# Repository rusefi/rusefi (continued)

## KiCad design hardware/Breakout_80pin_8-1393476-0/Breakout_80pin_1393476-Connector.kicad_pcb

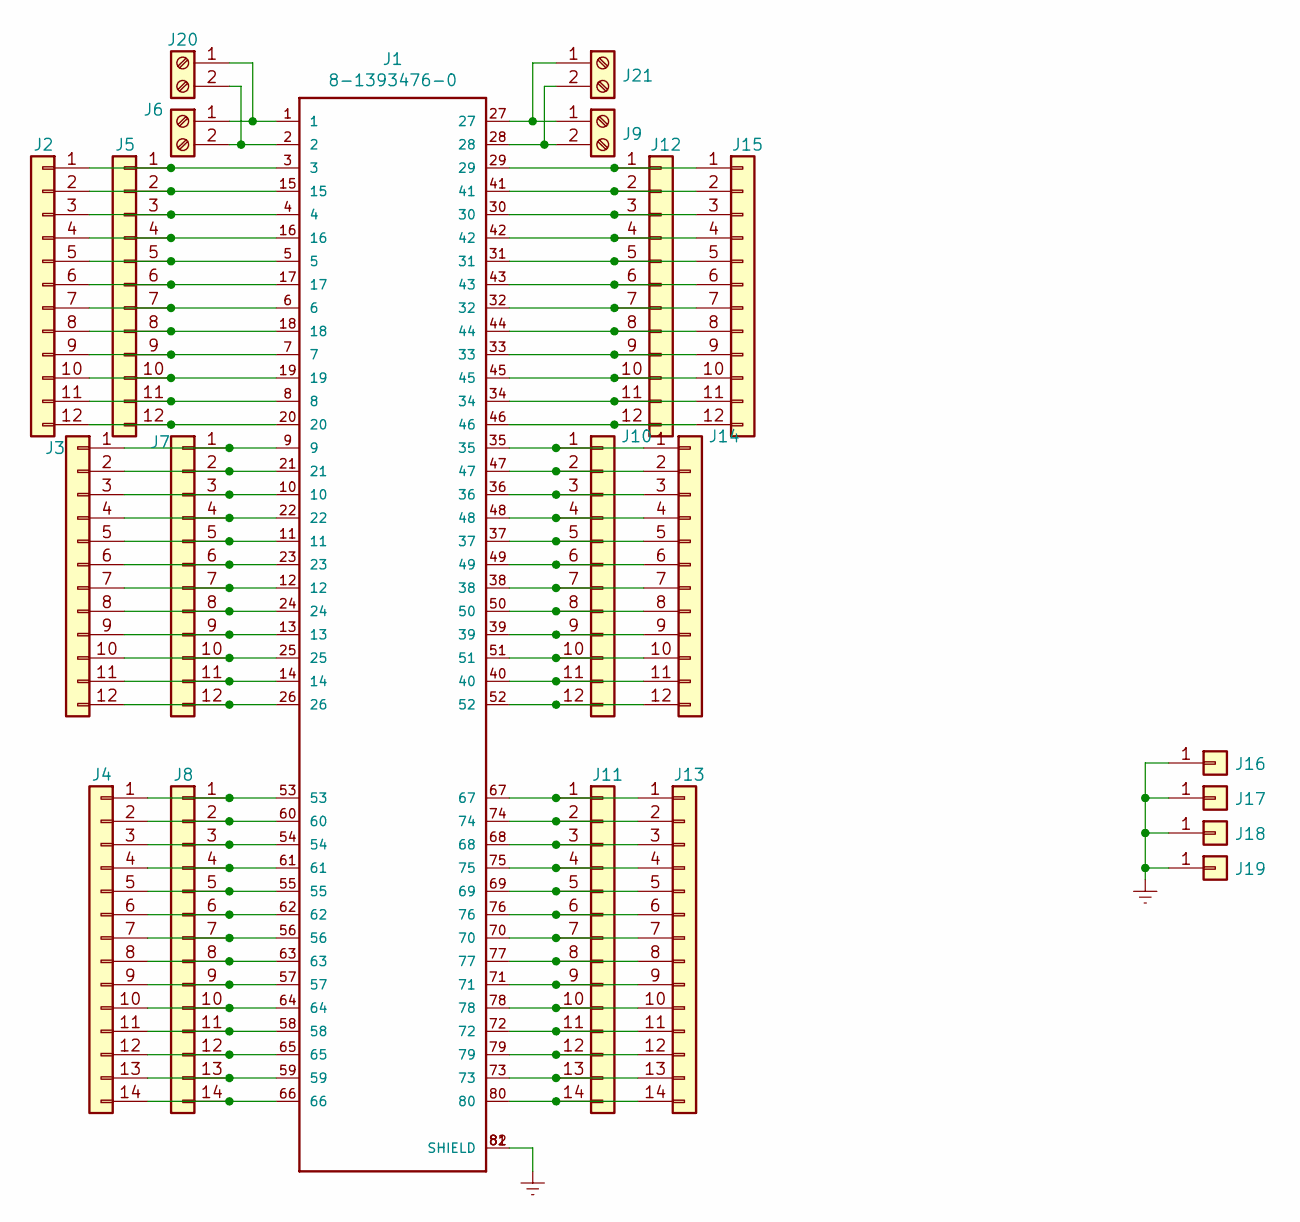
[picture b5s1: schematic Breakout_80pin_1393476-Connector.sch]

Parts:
J1: 8-1393476-0
J2, J3, J5, J7, J10, J12, J14, J15: Conn_01x12; Pin_Header_Straight_1x12_Pitch2.54mm
J4, J8, J11, J13: Conn_01x14; Pin_Header_Straight_1x14_Pitch2.54mm
J6, J9, J20, J21: Screw_Terminal_01x02; WireConnection_2.50mmDrill
J16, J17, J18, J19: Conn_01x01; Pin_Header_Straight_1x01_Pitch2.54mm

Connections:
Earth: J1.81 (SHIELD), J1.82 (SHIELD), J16.1, J17.1, J18.1, J19.1
unnamed: J1.1, J6.1, J20.1
unnamed: J1.2, J6.2, J20.2
unnamed: J1.3, J2.1, J5.1
unnamed: J1.4, J2.3, J5.3
unnamed: J1.5, J2.5, J5.5
unnamed: J1.6, J2.7, J5.7
unnamed: J1.7, J2.9, J5.9
unnamed: J1.8, J2.11, J5.11
unnamed: J1.9, J3.1, J7.1
unnamed: J1.10, J3.3, J7.3
unnamed: J1.11, J3.5, J7.5
unnamed: J1.12, J3.7, J7.7
unnamed: J1.13, J3.9, J7.9
unnamed: J1.14, J3.11, J7.11
unnamed: J1.15, J2.2, J5.2
unnamed: J1.16, J2.4, J5.4
unnamed: J1.17, J2.6, J5.6
unnamed: J1.18, J2.8, J5.8
unnamed: J1.19, J2.10, J5.10
unnamed: J1.20, J2.12, J5.12
unnamed: J1.21, J3.2, J7.2
unnamed: J1.22, J3.4, J7.4
unnamed: J1.23, J3.6, J7.6
unnamed: J1.24, J3.8, J7.8
unnamed: J1.25, J3.10, J7.10
unnamed: J1.26, J3.12, J7.12
unnamed: J1.27, J9.1, J21.1
unnamed: J1.28, J9.2, J21.2
unnamed: J1.29, J12.1, J15.1
unnamed: J1.30, J12.3, J15.3
unnamed: J1.31, J12.5, J15.5
unnamed: J1.32, J12.7, J15.7
unnamed: J1.33, J12.9, J15.9
unnamed: J1.34, J12.11, J15.11
unnamed: J1.35, J10.1, J14.1
unnamed: J1.36, J10.3, J14.3
unnamed: J1.37, J10.5, J14.5
unnamed: J1.38, J10.7, J14.7
unnamed: J1.39, J10.9, J14.9
unnamed: J1.40, J10.11, J14.11
unnamed: J1.41, J12.2, J15.2
unnamed: J1.42, J12.4, J15.4
unnamed: J1.43, J12.6, J15.6
unnamed: J1.44, J12.8, J15.8
unnamed: J1.45, J12.10, J15.10
unnamed: J1.46, J12.12, J15.12
unnamed: J1.47, J10.2, J14.2
unnamed: J1.48, J10.4, J14.4
unnamed: J1.49, J10.6, J14.6
unnamed: J1.50, J10.8, J14.8
unnamed: J1.51, J10.10, J14.10
unnamed: J1.52, J10.12, J14.12
unnamed: J1.53, J4.1, J8.1
unnamed: J1.54, J4.3, J8.3
unnamed: J1.55, J4.5, J8.5
unnamed: J1.56, J4.7, J8.7
unnamed: J1.57, J4.9, J8.9
unnamed: J1.58, J4.11, J8.11
unnamed: J1.59, J4.13, J8.13
unnamed: J1.60, J4.2, J8.2
unnamed: J1.61, J4.4, J8.4
unnamed: J1.62, J4.6, J8.6
unnamed: J1.63, J4.8, J8.8
unnamed: J1.64, J4.10, J8.10
unnamed: J1.65, J4.12, J8.12
unnamed: J1.66, J4.14, J8.14
unnamed: J1.67, J11.1, J13.1
unnamed: J1.68, J11.3, J13.3
unnamed: J1.69, J11.5, J13.5
unnamed: J1.70, J11.7, J13.7
unnamed: J1.71, J11.9, J13.9
unnamed: J1.72, J11.11, J13.11
unnamed: J1.73, J11.13, J13.13
unnamed: J1.74, J11.2, J13.2
unnamed: J1.75, J11.4, J13.4
unnamed: J1.76, J11.6, J13.6
unnamed: J1.77, J11.8, J13.8
unnamed: J1.78, J11.10, J13.10
unnamed: J1.79, J11.12, J13.12
unnamed: J1.80, J11.14, J13.14

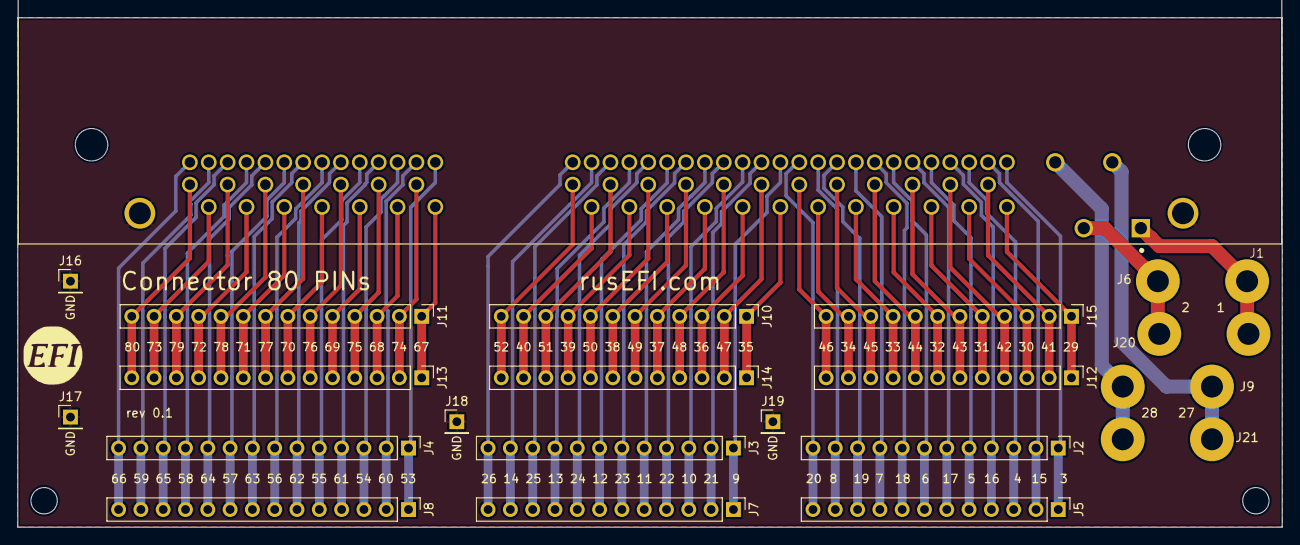
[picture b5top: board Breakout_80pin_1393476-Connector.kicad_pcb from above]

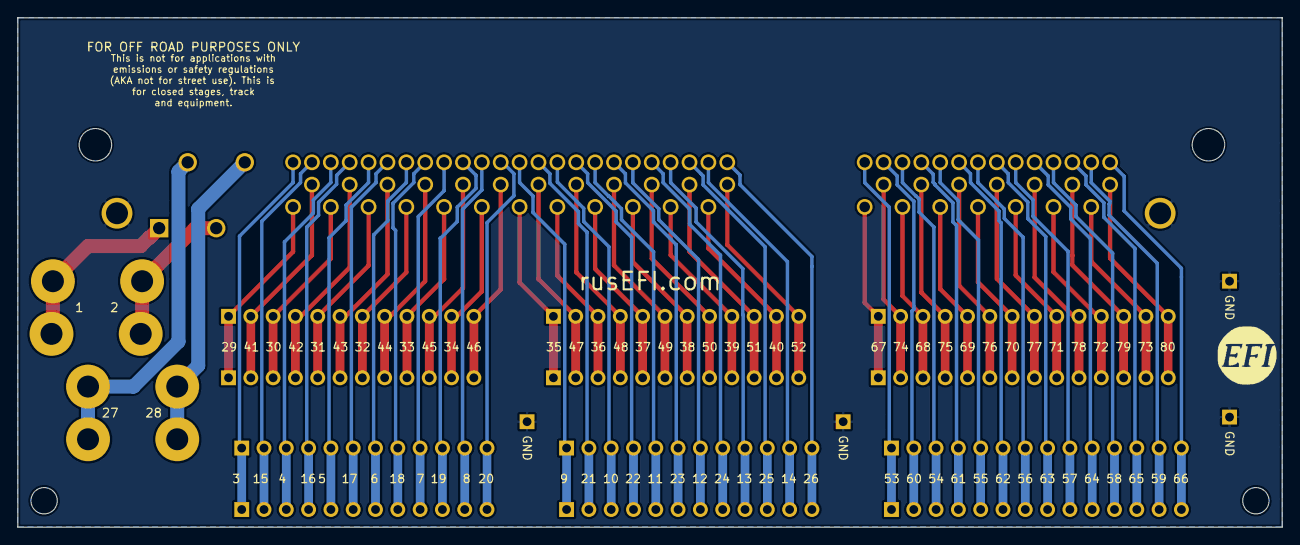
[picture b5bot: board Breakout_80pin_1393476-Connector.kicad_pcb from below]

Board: 2 copper layers, 144.0 x 58.0 mm, 24 parts (2 on the bottom side), 81 nets.

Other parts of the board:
G?: Disclaimer; Off_Road_Disclaimer
G?#2, G?#3: LOGO

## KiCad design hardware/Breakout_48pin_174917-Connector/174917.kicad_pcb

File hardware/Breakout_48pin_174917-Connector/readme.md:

48 pin breakout for Miata NA

As of March 2020 this was NEVER populated. Silkscreen might be not finished.

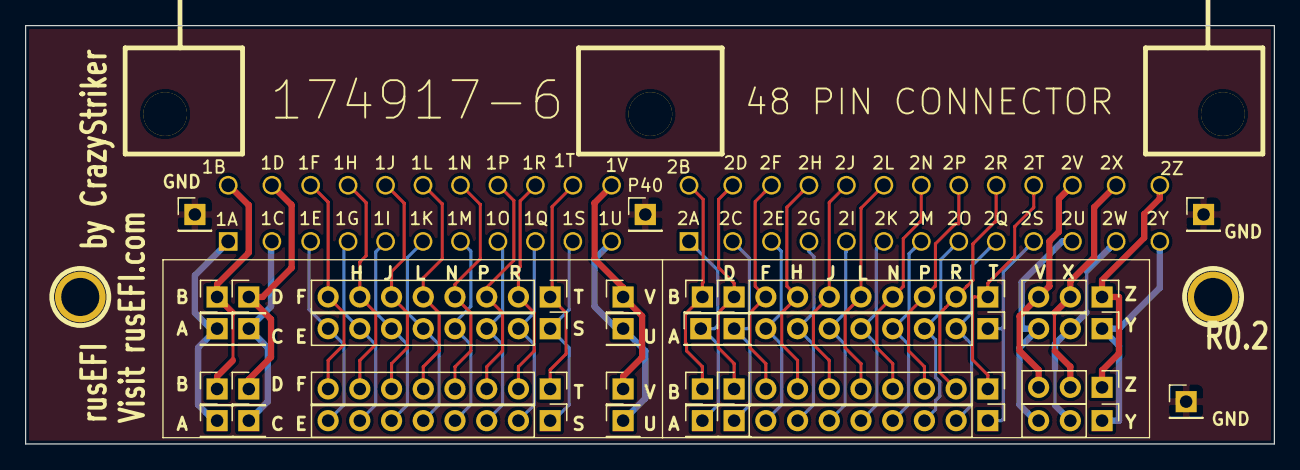
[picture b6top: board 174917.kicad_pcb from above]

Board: 2 copper layers, 100.0 x 33.5 mm, 39 parts (0 on the bottom side), 49 nets.

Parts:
1PIN, 1PIN#2: P***; 1pin
P1, P2, P13, P14: CONN_3; PinHeader_1x03_P2.54mm_Vertical
P3, P4, P5, P6, P7, P8, P9, P10, P11, P12, P15, P16, P17, P18, P19, P20, P21, P22, P23, P24, P38, P39, P40, P41: CONN_1; PinHeader_1x01_P2.54mm_Vertical
P25: 174917
P26, P27, P30, P31, P32, P33, P36, P37: CONN_8; PinHeader_1x08_P2.54mm_Vertical

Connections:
GND: P38.1, P39.1, P40.1, P41.1
unnamed: P1.1, P13.1
unnamed: P1.2, P13.2
unnamed: P1.3, P13.3
unnamed: P10.1, P22.1
unnamed: P11.1, P23.1
unnamed: P12.1, P24.1
unnamed: P2.1, P14.1
unnamed: P2.2, P14.2
unnamed: P2.3, P14.3
unnamed: P3.1, P15.1
unnamed: P4.1, P16.1
unnamed: P5.1, P17.1
unnamed: P6.1, P18.1
unnamed: P7.1, P19.1
unnamed: P8.1, P20.1
unnamed: P9.1, P21.1
unnamed: P26.1, P32.1
unnamed: P26.3, P32.3
unnamed: P26.4, P32.4
unnamed: P26.5, P32.5
unnamed: P26.6, P32.6
unnamed: P26.7, P32.7
unnamed: P26.8, P32.8
unnamed: P27.1, P33.1
unnamed: P27.2, P33.2
unnamed: P27.3, P33.3
unnamed: P27.4, P33.4
unnamed: P27.5, P33.5
unnamed: P27.6, P33.6
unnamed: P27.7, P33.7
unnamed: P27.8, P33.8
unnamed: P30.1, P36.1
unnamed: P30.2, P36.2
unnamed: P30.3, P36.3
unnamed: P30.4, P36.4
unnamed: P30.5, P36.5
unnamed: P30.6, P36.6
unnamed: P30.7, P36.7
unnamed: P30.8, P36.8
unnamed: P31.1, P37.1
unnamed: P31.2, P37.2
unnamed: P31.3, P37.3
unnamed: P31.4, P37.4
unnamed: P31.5, P37.5
unnamed: P31.6, P37.6
unnamed: P31.7, P37.7
unnamed: P31.8, P37.8
unnamed: P26.2, P32.2

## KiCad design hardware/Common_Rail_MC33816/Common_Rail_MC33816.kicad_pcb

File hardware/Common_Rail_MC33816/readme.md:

https://rusefi.com/forum/viewtopic.php?f=4&t=1337

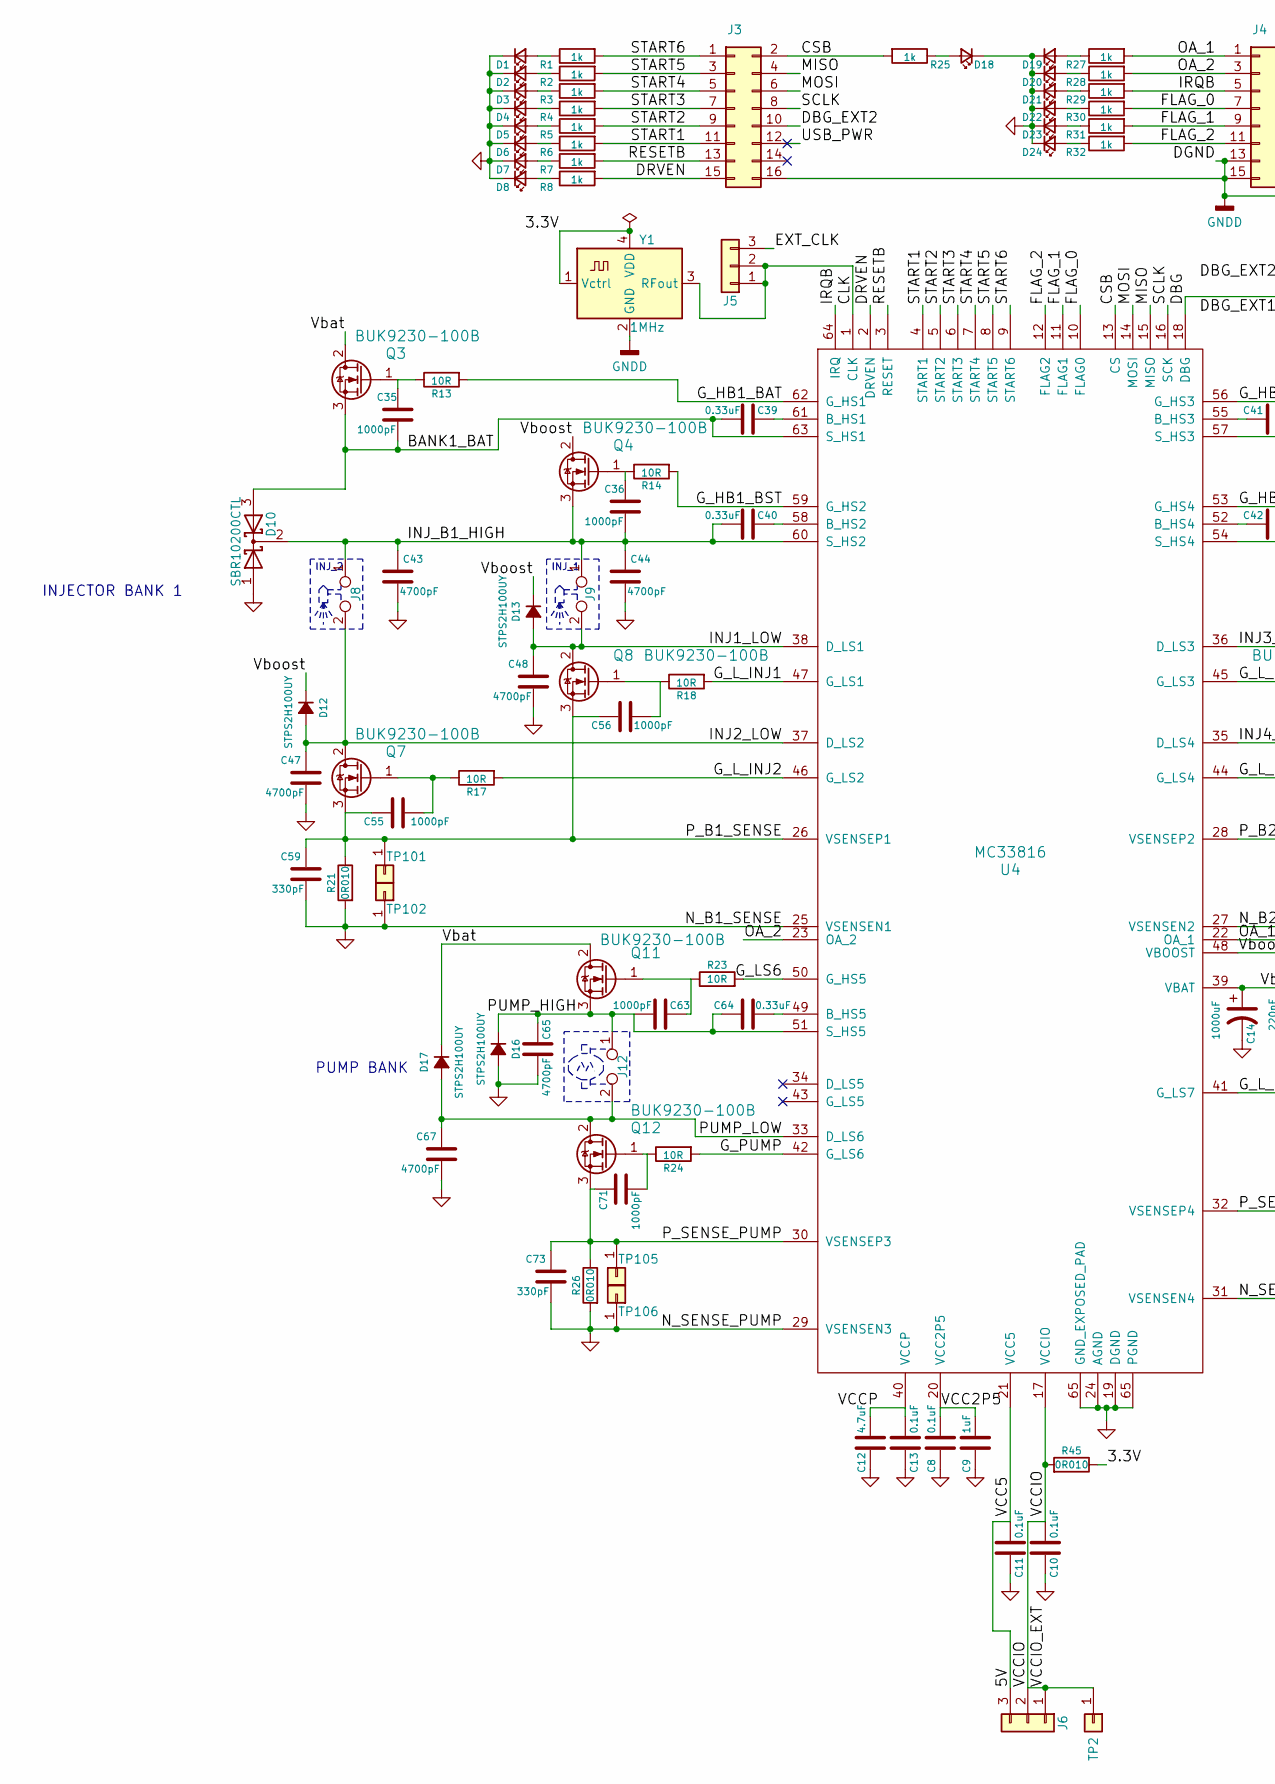
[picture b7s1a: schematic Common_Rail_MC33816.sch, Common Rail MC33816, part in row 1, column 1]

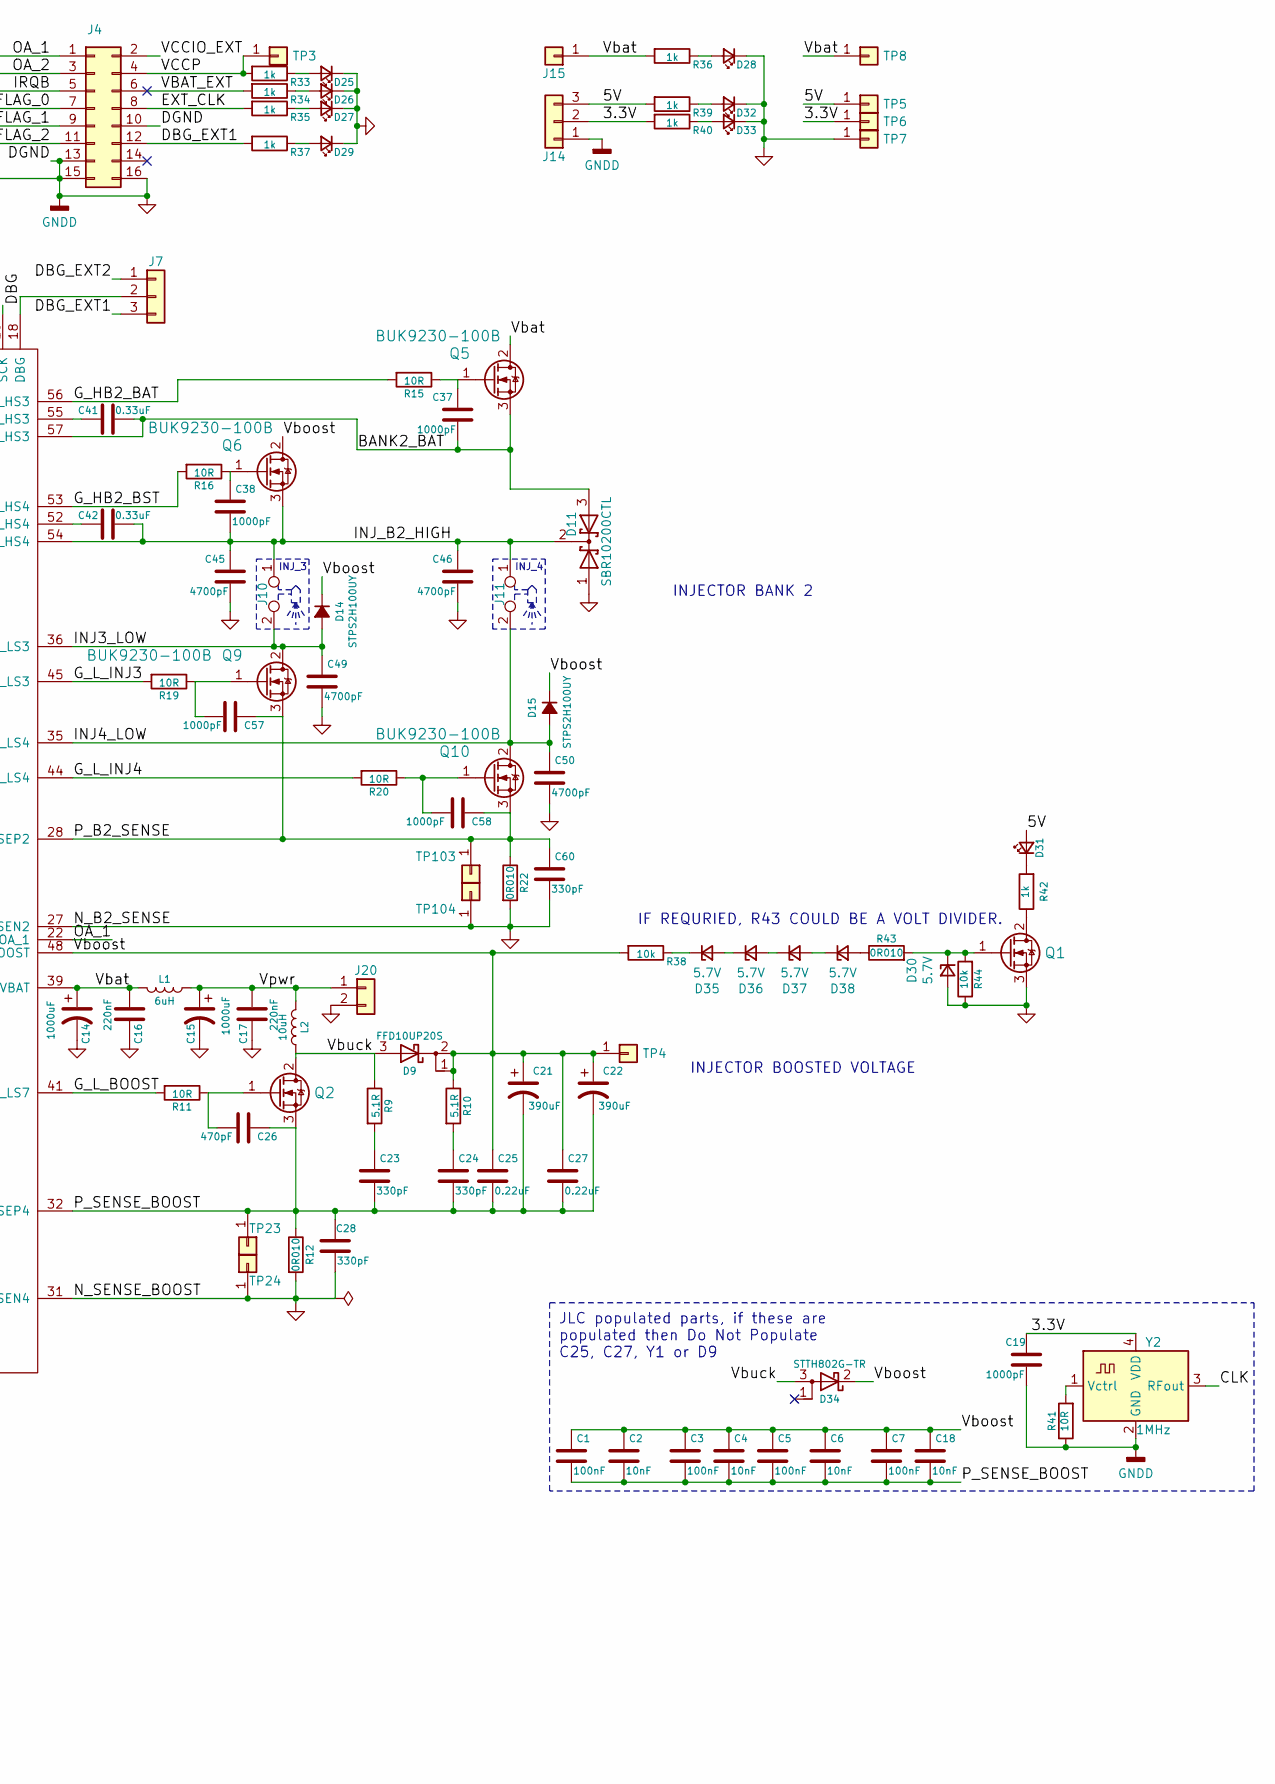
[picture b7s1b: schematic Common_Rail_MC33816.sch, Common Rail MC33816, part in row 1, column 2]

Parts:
C1, C3, C5, C7: 100nF; C_0805; LCSC C28233
C2, C4, C6, C18: 10nF; C_0805; LCSC C18741
C8, C10, C11, C13: 0.1uF; C_0805; LCSC C49678
C9: 1uF; C_0805; LCSC C28323
C12: 4.7uF; C_0805; LCSC C1779
C14, C15: 1000uF; CP_Radial_D22.0mm_P10.00mm_SnapIn
C16, C17: 220nF; C_0805; LCSC C5378
C19, C35, C36, C37, C38, C55, C56, C57, C58, C63, C71: 1000pF; C_0805; LCSC C46653
C21, C22: 390uF; CP_Radial_D16.0mm_P7.50mm
C23, C24, C28, C59, C60, C73: 330pF; C_0805; LCSC C51207
C25, C27: 0.22uF; C_0805
C26: 470pF; C_0805; LCSC C1743
C39, C40, C41, C42, C64: 0.33uF; C_0805; LCSC C1740
C43, C44, C45, C46, C47, C48, C49, C50, C65, C67: 4700pF; C_0805; LCSC C21217
D1, D2, D3, D4, D5, D6, D7, D8, D18, D19, D20, D21, D22, D23, D24, D25, D26, D27, D28, D29, D31, D32, D33: LED_Small; LED_0805_2012Metric; LCSC C2296
D9: FFD10UP20S; TO-252-2
D10, D11: SBR10200CTL; TO-252-2; LCSC C135494
D12, D13, D14, D15, D16, D17: STPS2H100UY; D_SMB; LCSC C157420
D30, D35, D36, D37, D38: 5.7V; D_MicroMELF_Handsoldering; LCSC C8062
D34: STTH802G-TR; TO-263-2; LCSC C181034
J3, J4: CONN_02X08; Pin_Header_Straight_2x08_Pitch2.54mm
J5, J6, J7, J14: CONN_01X03; Pin_Header_Straight_1x03_Pitch2.54mm
J8, J9, J10, J11, J12: INJ_Term; TerminalBlock_bornier-2_P5.08mm
J15: CONN_01X01; Pin_D1.4mm_L8.5mm_W2.8mm_FlatFork
J20: Conn_01x02; TerminalBlock_bornier-2_P5.08mm
L1: 6uH; 744710610-Inductor
L2: 10uH; IHLP6767GZER100M01
Q1, Q2, Q3, Q4, Q5, Q6, Q7, Q8, Q9, Q10, Q11, Q12: BUK9230-100B; TO-252-2; LCSC C67277
R1, R2, R3, R4, R5, R6, R7, R8, R25, R27, R28, R29, R30, R31, R32, R33, R34, R35, R36, R37, R39, R40: 1k; R_0805; LCSC C17513
R9, R10: 5.1R; R_0805; LCSC C247080
R11, R13, R14, R15, R16, R17, R18, R19, R20, R23, R24, R41: 10R; R_0805; LCSC C17415
R12, R21, R22, R26: 0R010; R_1206_HandSoldering; LCSC C76294
R38, R44: 10k; R_0603_1608Metric; LCSC C17513
R42: 1k; R_0805_2012Metric; LCSC C17513
R43, R45: 0R010; R_1206_3216Metric_Pad1.42x1.75mm_HandSolder; LCSC C76294
TP2, TP3, TP4, TP5, TP6, TP7, TP8, TP23, TP24, TP101, TP102, TP103, TP104, TP105, TP106: CONN_01X01; Pin_D0.7mm_L6.5mm_W1.8mm_FlatFork
U4: MC33816; HTQFP-64-1EP_10x10mm_Pitch0.5mm_ThermalPad_for_MC33816
Y1: 1MHz; Crystal_SMD_SeikoEpson_MC306-4pin_8.0x3.2mm
Y2: 1MHz; Oscillator_SMD_Diodes_FN-4Pin_7.0x5.0mm; LCSC C70608

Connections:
/3.3V: C19.1, J14.2, R40.2, R45.1, TP6.1, Y1.1 (Vctrl), Y1.4 (VDD), Y2.4 (VDD)
/5V: C11.1, D31.2 (A), J6.3, J14.3, R39.2, TP5.1, U4.21 (VCC5)
/BANK1_BAT: C35.2, C39.2, D10.3 (A), Q3.3 (S), U4.63 (S_HS1)
/BANK2_BAT: C37.2, C41.2, D11.3 (A), Q5.3 (S), U4.57 (S_HS3)
/CLK: J5.1, J5.2, U4.1 (CLK), Y1.3 (RFout), Y2.3 (RFout)
/CSB: J3.2, R25.2, U4.13 (CS)
/DBG: J7.2, U4.18 (DBG)
/DBG_EXT1: J4.12, J7.3, R37.2
/DBG_EXT2: J3.10, J7.1
/DRVEN: J3.15, R8.2, U4.2 (DRVEN)
/EXT_CLK: J4.8, J5.3, R35.2
/FLAG_0: J4.7, R30.2, U4.10 (FLAG0)
/FLAG_1: J4.9, R31.2, U4.11 (FLAG1)
/FLAG_2: J4.11, R32.2, U4.12 (FLAG2)
/G_HB1_BAT: R13.2, U4.62 (G_HS1)
/G_HB1_BST: R14.2, U4.59 (G_HS2)
/G_HB2_BAT: R15.2, U4.56 (G_HS3)
/G_HB2_BST: R16.2, U4.53 (G_HS4)
/G_LS6: R23.2, U4.50 (G_HS5)
/G_L_BOOST: R11.2, U4.41 (G_LS7)
/G_L_INJ1: R18.2, U4.47 (G_LS1)
/G_L_INJ2: R17.2, U4.46 (G_LS2)
/G_L_INJ3: R19.2, U4.45 (G_LS3)
/G_L_INJ4: R20.2, U4.44 (G_LS4)
/G_PUMP: R24.2, U4.42 (G_LS6)
/INJ1_LOW: C48.1, D13.2 (A), J9.2, Q8.2 (D), U4.38 (D_LS1)
/INJ2_LOW: C47.1, D12.2 (A), J8.2, Q7.2 (D), U4.37 (D_LS2)
/INJ3_LOW: C49.1, D14.2 (A), J10.2, Q9.2 (D), U4.36 (D_LS3)
/INJ4_LOW: C50.1, D15.2 (A), J11.2, Q10.2 (D), U4.35 (D_LS4)
/INJ_B1_HIGH: C36.2, C40.2, C43.1, C44.1, D10.2 (K), J8.1, J9.1, Q4.3 (S), U4.60 (S_HS2)
/INJ_B2_HIGH: C38.2, C42.2, C45.1, C46.1, D11.2 (K), J10.1, J11.1, Q6.3 (S), U4.54 (S_HS4)
/IRQB: J4.5, R29.2, U4.64 (IRQ)
/MISO: J3.4, U4.15 (MISO)
/MOSI: J3.6, U4.14 (MOSI)
/OA_1: J4.1, R27.2, U4.22 (OA_1)
/OA_2: J4.3, R28.2, U4.23 (OA_2)
/PUMP_HIGH: C63.2, C64.1, C65.1, D16.1 (K), J12.1, Q11.3 (S), U4.51 (S_HS5)
/PUMP_LOW: C67.1, D17.2 (A), J12.2, Q12.2 (D), U4.33 (D_LS6)
/P_B1_SENSE: C55.1, C56.1, C59.1, Q7.3 (S), Q8.3 (S), R21.1, TP101.1, U4.26 (VSENSEP1)
/P_B2_SENSE: C57.1, C58.1, C60.1, Q9.3 (S), Q10.3 (S), R22.1, TP103.1, U4.28 (VSENSEP2)
/P_SENSE_BOOST: C1.2, C2.2, C3.2, C4.2, C5.2, C6.2, C7.2, C18.2, C21.2, C22.2, C23.2, C24.2, C25.2, C26.1, C27.2, C28.1, Q2.3 (S), R12.1, TP23.1, U4.32 (VSENSEP4)
/P_SENSE_PUMP: C71.1, C73.1, Q12.3 (S), R26.1, TP105.1, U4.30 (VSENSEP3)
/RESETB: J3.13, R7.2, U4.3 (RESET)
/SCLK: J3.8, U4.16 (SCK)
/START1: J3.11, R6.2, U4.4 (START1)
/START2: J3.9, R5.2, U4.5 (START2)
/START3: J3.7, R4.2, U4.6 (START3)
/START4: J3.5, R3.2, U4.7 (START4)
/START5: J3.3, R2.2, U4.8 (START5)
/START6: J3.1, R1.2, U4.9 (START6)
/VBAT_EXT: J4.6, R34.2
/VCC2P5: C8.1, C9.1, U4.20 (VCC2P5)
/VCCIO: C10.1, J4.2, J6.1, J6.2, R45.2, TP2.1, U4.17 (VCCIO)
/VCCP: C12.1, C13.1, J4.4, R33.2, TP3.1, U4.40 (VCCP)
/Vbat: C14.1, C16.1, D17.1 (K), J15.1, L1.2, Q3.2 (D), Q5.2 (D), Q11.2 (D), R36.2, TP8.1, U4.39 (VBAT)
/Vboost: C1.1, C2.1, C3.1, C4.1, C5.1, C6.1, C7.1, C18.1, C21.1, C22.1, C25.1, C27.1, D9.1 (K), D9.2 (K), D12.1 (K), D13.1 (K), D14.1 (K), D15.1 (K), D34.2 (K), Q4.2 (D), Q6.2 (D), R10.1, R38.2, TP4.1, U4.48 (VBOOST)
/Vbuck: D9.3 (A), D34.3 (A), L2.1, Q2.2 (D), R9.1
/Vpwr: C15.1, C17.1, J20.1, L1.1, L2.2
GND: C8.2, C9.2, C10.2, C11.2, C12.2, C13.2, C14.2, C15.2, C16.2, C17.2, C19.2, C28.2, C43.2, C44.2, C45.2, C46.2, C47.2, C48.2, C49.2, C50.2, C59.2, C60.2, C65.2, C67.2, C73.2, D1.1 (K), D2.1 (K), D3.1 (K), D4.1 (K), D5.1 (K), D6.1 (K), D7.1 (K), D8.1 (K), D10.1 (A), D11.1 (A), D16.2 (A), D18.1 (K), D19.1 (K), D20.1 (K), D21.1 (K), D22.1 (K), D23.1 (K), D24.1 (K), D25.1 (K), D26.1 (K), D27.1 (K), D28.1 (K), D29.1 (K), D30.2 (A), D32.1 (K), D33.1 (K), J3.16, J4.10, J4.13, J4.15, J4.16, J14.1, J20.2, Q1.3 (S), R12.2, R21.2, R22.2, R26.2, R41.1, R44.1, TP7.1, TP24.1, TP102.1, TP104.1, TP106.1, U4.19 (DGND), U4.24 (AGND), U4.25 (VSENSEN1), U4.27 (VSENSEN2), U4.29 (VSENSEN3), U4.31 (VSENSEN4), U4.65 (GND_EXPOSED_PAD), Y1.2 (GND), Y2.2 (GND)
unnamed: C23.1, R9.2
unnamed: C24.1, R10.2
unnamed: C26.2, Q2.1 (G), R11.1
unnamed: C35.1, Q3.1 (G), R13.1
unnamed: C36.1, Q4.1 (G), R14.1
unnamed: C37.1, Q5.1 (G), R15.1
unnamed: C38.1, Q6.1 (G), R16.1
unnamed: C39.1, U4.61 (B_HS1)
unnamed: C40.1, U4.58 (B_HS2)
unnamed: C41.1, U4.55 (B_HS3)
unnamed: C42.1, U4.52 (B_HS4)
unnamed: C55.2, Q7.1 (G), R17.1
unnamed: C56.2, Q8.1 (G), R18.1
unnamed: C57.2, Q9.1 (G), R19.1
unnamed: C58.2, Q10.1 (G), R20.1
unnamed: C63.1, Q11.1 (G), R23.1
unnamed: C64.2, U4.49 (B_HS5)
unnamed: C71.2, Q12.1 (G), R24.1
unnamed: D1.2 (A), R1.1
unnamed: D2.2 (A), R2.1
unnamed: D3.2 (A), R3.1
unnamed: D4.2 (A), R4.1
unnamed: D5.2 (A), R5.1
unnamed: D6.2 (A), R6.1
unnamed: D7.2 (A), R7.1
unnamed: D8.2 (A), R8.1
unnamed: D18.2 (A), R25.1
unnamed: D19.2 (A), R27.1
unnamed: D20.2 (A), R28.1
unnamed: D21.2 (A), R29.1
unnamed: D22.2 (A), R30.1
unnamed: D23.2 (A), R31.1
unnamed: D24.2 (A), R32.1
unnamed: D25.2 (A), R33.1
unnamed: D26.2 (A), R34.1
unnamed: D27.2 (A), R35.1
unnamed: D28.2 (A), R36.1
unnamed: D29.2 (A), R37.1
unnamed: D30.1 (K), Q1.1 (G), R43.2, R44.2
unnamed: D31.1 (K), R42.2
unnamed: D32.2 (A), R39.1
unnamed: D33.2 (A), R40.1
unnamed: D35.1 (K), R38.1
unnamed: D35.2 (A), D36.1 (K)
unnamed: D36.2 (A), D37.1 (K)
unnamed: D37.2 (A), D38.1 (K)
unnamed: D38.2 (A), R43.1
unnamed: Q1.2 (D), R42.1
unnamed: R41.2, Y2.1 (Vctrl)

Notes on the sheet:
PUMP BANK
INJECTOR BOOSTED VOLTAGE
INJECTOR BANK 2
INJECTOR BANK 1
INJ_2
INJ_1
INJ_3
INJ_4
JLC populated parts, if these are populated then Do Not Populate C25, C27, Y1 or D9
IF REQURIED, R43 COULD BE A VOLT DIVIDER.

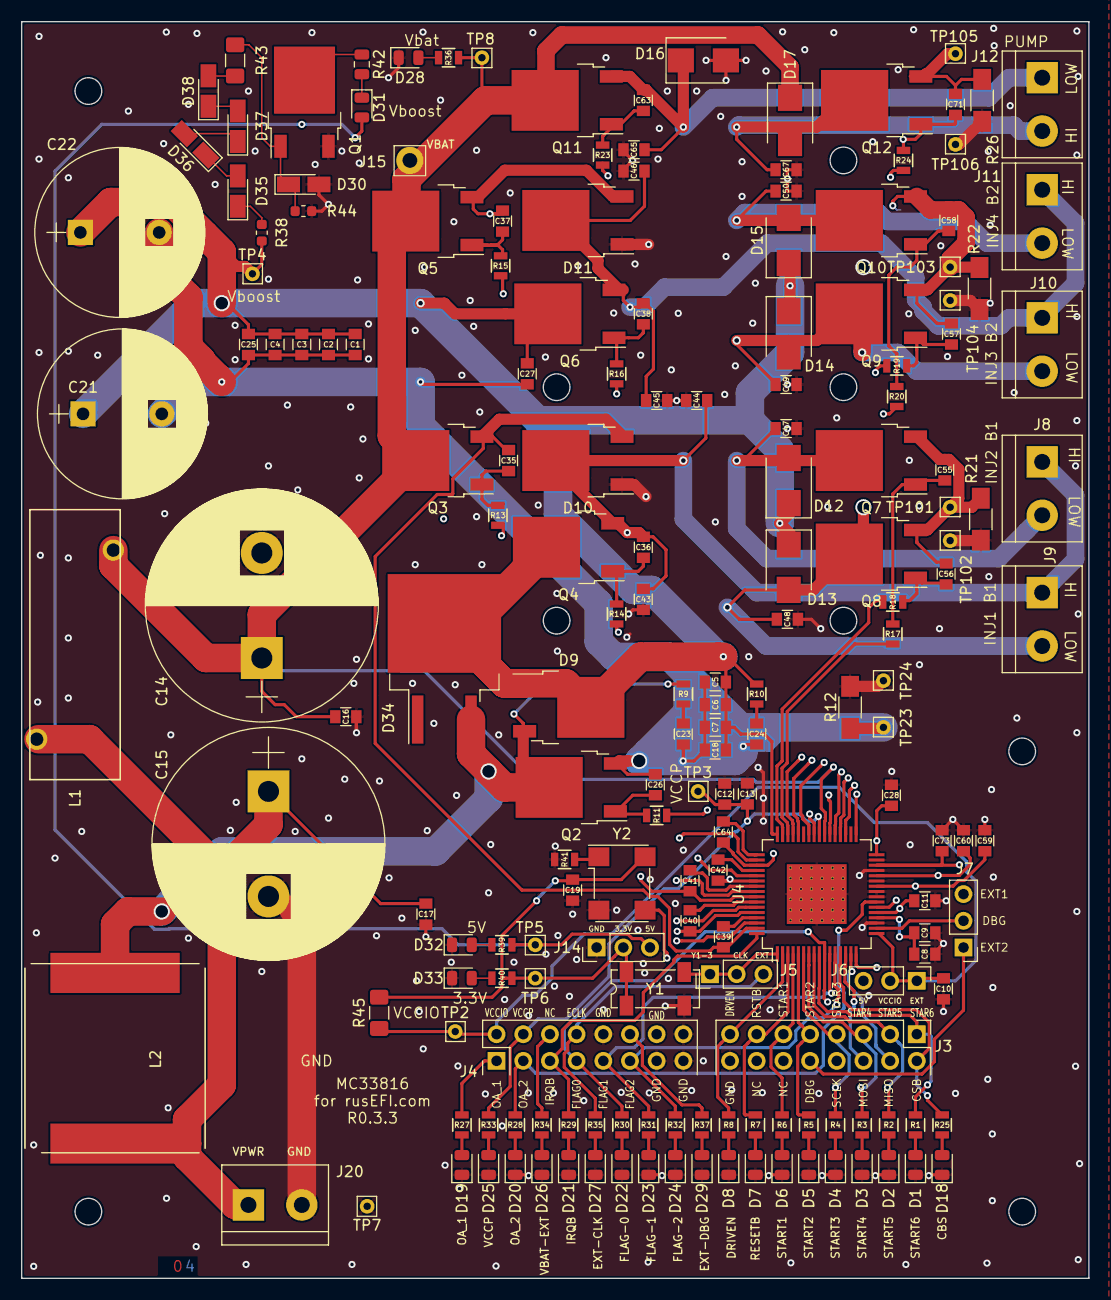
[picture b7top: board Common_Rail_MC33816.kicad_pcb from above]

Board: 4 copper layers, 101.6 x 119.6 mm, 183 parts (0 on the bottom side), 108 nets.

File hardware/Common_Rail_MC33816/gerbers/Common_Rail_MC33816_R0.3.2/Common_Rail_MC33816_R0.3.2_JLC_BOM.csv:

Comment,Designator,Footprint,LCSC, LCSC, MFG,MFG#, VEND1,VEND1#, VEND2,VEND2#
"100nF","C1,C3,C5,C7","rusefi_lib:C_0805","","C28233","","",""
"0.1uF","C10,C11,C13,C8","rusefi_lib:C_0805","","C49678","AVX,08055C104MAT2A","DIGI,478-3351-1-ND","JLCPCB,C49678"
"4.7uF","C12","rusefi_lib:C_0805","","C1779","Taiyo Yuden,TMK212AB7475KG-T","DIGI,587-2990-1-ND","JLCPCB,C1779"
"1000uF","C14,C15","Capacitors_ThroughHole:CP_Radial_D22.0mm_P10.00mm_SnapIn","","","Cornell,SLPX102M100A3P3","DIGI,338-1553-ND",","
"220nF","C17,C16","rusefi_lib:C_0805","","C5378","KEMET,C0805C224M1RACTU","DIGI,399-9205-1-ND",","
"10nF","C2,C4,C6,C18","rusefi_lib:C_0805","","C18741","","",""
"390uF","C21,C22","Capacitors_ThroughHole:CP_Radial_D16.0mm_P7.50mm","","","Nichicon,UHE2A391MHD","DIGI,493-1680-ND",","
"0.22uF","C25,C27","rusefi_lib:C_0805","","","KEMET,C0805C224M1RACTU","DIGI,399-9205-1-ND",","
"470pF","C26","rusefi_lib:C_0805","","C1743","TDK,CGA4C2C0G2A471J060AA","DIGI,445-6953-1-ND","JLCPCB,C1743"
"1000pF","C38,C37,C57,C58,C63,C71,C36,C35,C56,C55,C19","rusefi_lib:C_0805","","C46653","avx,08051C102KAT2A","DIGI,478-1352-1-ND","JLCPCB,C209838"
"0.33uF","C41,C64,C39,C40,C42","rusefi_lib:C_0805","","C1740","Yageo,CC0805KKX7R8BB334","DIGI,311-3385-1-ND","JLCPCB,C1740"
"4700pF","C45,C49,C46,C50,C65,C67,C44,C48,C43,C47","rusefi_lib:C_0805","","C21217","TDK,C2012C0G2A472J125AA","DIGI,445-2324-1-ND","JLCPCB,C21217"
"330pF","C60,C23,C24,C28,C73,C59","rusefi_lib:C_0805","","C51207","Kemet,C0805C331J1GACTU","DIGI,399-1131-1-ND","JLCPCB,C51207"
"1uF","C9","rusefi_lib:C_0805","","C28323","Yageo,CC0805KKX7R8BB105","DIGI,311-1456-1-ND","JLCPCB,C28323"
"SBR10200CTL","D11,D10","Package_TO_SOT_SMD:TO-252-2","","C135494","Diodes,SBR10200CTL-13","DIGI,SBR10200CTL-13DICT-ND",","
"STPS2H100UY","D17,D14,D15,D16,D13,D12","Diodes_SMD:D_SMB","","C157420","ST,STPS2H100UY","DIGI,497-11093-1-ND",","
"LED_Small","D26,D25,D27,D29,D2,D1,D4,D3,D5,D6,D7,D8,D19,D18,D20,D21,D22,D23,D24,D31,D32,D28,D33","LED_SMD:LED_0805_2012Metric","","C2296","","",""
"5.7V","D30,D41,D40,D39,D38,D37,D36,D35","Diode_SMD:D_MicroMELF_Handsoldering","","C8062","","",""
"STTH802G-TR","D34","Package_TO_SOT_SMD:TO-263-2","","C181034","","",""
"FFD10UP20S","D9","Package_TO_SOT_SMD:TO-252-2","","","ONSEMI,FFD10UP20S","DIGI,FFD10UP20SCT-ND",","
"INJ_Term","J10,J11,J9","TerminalBlock:TerminalBlock_bornier-2_P5.08mm","","","onshore,OSTTG025100B","DIGI,ED2703-ND",","
"CONN_01X01","J15","Connector_Pin:Pin_D1.4mm_L8.5mm_W2.8mm_FlatFork",""
"Conn_01x02","J20","TerminalBlock:TerminalBlock_bornier-2_P5.08mm","","","TE,282834-2","DIGI,A98333-ND",""
"CONN_02X08","J3,J4","Pin_Headers:Pin_Header_Straight_2x08_Pitch2.54mm","","","sullins,SBH11-PBPC-D08-ST-BK","DIGI,S9171-ND",","
"CONN_01X03","J7,J5,J6,J14","Pin_Headers:Pin_Header_Straight_1x03_Pitch2.54mm",""
"INJ_Term","J8,J12","Terminal_Blocks:TerminalBlock_bornier-2_P5.08mm","","","onshore,OSTTG025100B","DIGI,ED2703-ND",","
"6uH","L1","rusefi_lib:744710610-Inductor","","","Würth Elektronik,744710610","DIGI,732-3255-ND",","
"10uH","L2","rusefi_lib:IHLP6767GZER100M01","","","Vishay,IHLP6767GZER100M01","DIGI,541-1259-1-ND",","
"BUK9230-100B","Q6,Q5,Q9,Q10,Q11,Q2,Q12,Q4,Q3,Q8,Q7","Package_TO_SOT_SMD:TO-252-2","","C67277 ","Nexperia,BUK9230-100B","DIGI,1727-4708-1-ND",","
"10R","R16,R15,R19,R20,R11,R23,R24,R14,R13,R18,R17,R41","rusefi_lib:R_0805","","C17415","Stackpole,RMCF0805JG10R0","DIGI,RMCF0805JG10R0CT-ND","JLCPCB,C17403"
"0R010","R22,R12,R26,R21","Resistors_SMD:R_1206_HandSoldering","","C76294","Panasonic,ERJ-8CWFR015V","DIGI,P0.015BVCT-ND","JLCPCB,C201281"
"1k","R34,R33,R35,R37,R2,R1,R4,R3,R5,R6,R7,R8,R27,R25,R28,R29,R30,R31,R32,R38,R39,R36,R40","rusefi_lib:R_0805","","C17513"," , "," , ",","
"5.1R","R9,R10","rusefi_lib:R_0805","","C247080","Stackpole,RMCF0805JT5R10","DIGI,RMCF0805JT5R10CT-ND","JLCPCB,C247080"
"CONN_01X01","TP23,TP24,TP103,TP104,TP101,TP102,TP105,TP106,TP4,TP7,TP3,TP6,TP5,TP2,TP8","Connector_Pin:Pin_D0.7mm_L6.5mm_W1.8mm_FlatFork",""
"AMS1117-3.3","U1","Package_TO_SOT_SMD:SOT-223","","C6186","","",""
"MC33816","U4","rusefi_lib:HTQFP-64-1EP_10x10mm_Pitch0.5mm_ThermalPad_for_MC33816","","","FreeScale,MC33816AE","Mouser,841-MC33816AE",","
"1MHz","Y1","Crystals:Crystal_SMD_SeikoEpson_MC306-4pin_8.0x3.2mm","","","epson,SG7050CAN 1.000000M-TJGA3","DIGI,SER3990CT-ND",""
"1MHz","Y2","Oscillator:Oscillator_SMD_Diodes_FN-4Pin_7.0x5.0mm","","C70608","","",""

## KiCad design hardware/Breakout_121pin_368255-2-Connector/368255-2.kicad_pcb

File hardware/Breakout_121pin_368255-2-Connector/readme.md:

121 pin Audi VW Nissan Hyundai

# [PCB for sale here](https://www.tindie.com/products/russian/ecu-121p-connector-bare-pcb/)

# [Connector for sale here](https://www.tindie.com/products/russian/121-pin-ecu-connector/)

[Forum thread](https://rusefi.com/forum/viewtopic.php?t=208)

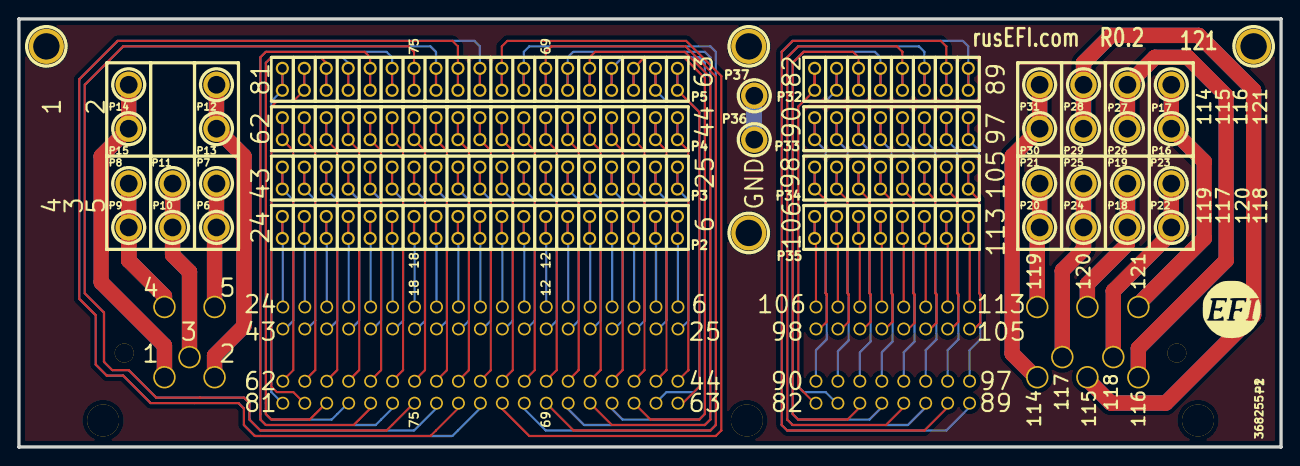
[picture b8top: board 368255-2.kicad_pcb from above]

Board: 2 copper layers, 146.1 x 49.5 mm, 43 parts (1 on the bottom side), 122 nets.

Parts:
1PIN, 1PIN#2, 1PIN#3, 1PIN#4: P***; 1pin
G?: LOGO
G?#2: LOGO; LOGO_F
P1: 368255-2
P2, P3, P4, P5: CONN_19; 19dpad
P6, P7, P8, P9, P10, P11, P12, P13, P14, P15, P16, P17, P18, P19, P20, P21, P22, P23, P24, P25, P26, P27, P28, P29, P30, P31, P36, P37: CONN_1; 1pin(m)
P32, P33, P34, P35: CONN_8; 8dpad

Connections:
GND: P36.1, P37.1
unnamed: P1.22, P2.17
unnamed: P1.34, P3.10
unnamed: P1.33, P3.9
unnamed: P1.32, P3.8
unnamed: P1.31, P3.7
unnamed: P1.30, P3.6
unnamed: P1.29, P3.5
unnamed: P1.28, P3.4
unnamed: P1.27, P3.3
unnamed: P1.26, P3.2
unnamed: P1.25, P3.1
unnamed: P1.24, P2.19
unnamed: P1.23, P2.18
unnamed: P1.35, P3.11
unnamed: P1.21, P2.16
unnamed: P1.20, P2.15
unnamed: P1.19, P2.14
unnamed: P1.18, P2.13
unnamed: P1.17, P2.12
unnamed: P1.16, P2.11
unnamed: P1.15, P2.10
unnamed: P1.14, P2.9
unnamed: P1.13, P2.8
unnamed: P1.12, P2.7
unnamed: P1.11, P2.6
unnamed: P1.10, P2.5
unnamed: P1.48, P4.5
unnamed: P1.60, P4.17
unnamed: P1.59, P4.16
unnamed: P1.58, P4.15
unnamed: P1.57, P4.14
unnamed: P1.56, P4.13
unnamed: P1.55, P4.12
unnamed: P1.54, P4.11
unnamed: P1.53, P4.10
unnamed: P1.52, P4.9
unnamed: P1.51, P4.8
unnamed: P1.50, P4.7
unnamed: P1.49, P4.6
unnamed: P1.9, P2.4
unnamed: P1.47, P4.4
unnamed: P1.46, P4.3
unnamed: P1.45, P4.2
unnamed: P1.44, P4.1
unnamed: P1.43, P3.19
unnamed: P1.42, P3.18
unnamed: P1.41, P3.17
unnamed: P1.40, P3.16
unnamed: P1.39, P3.15
unnamed: P1.38, P3.14
unnamed: P1.37, P3.13
unnamed: P1.36, P3.12
unnamed: P1.94, P33.5
unnamed: P1.106, P35.1
unnamed: P1.105, P34.8
unnamed: P1.104, P34.7
unnamed: P1.103, P34.6
unnamed: P1.102, P34.5
unnamed: P1.101, P34.4
unnamed: P1.100, P34.3
unnamed: P1.99, P34.2
unnamed: P1.98, P34.1
unnamed: P1.97, P33.8
unnamed: P1.96, P33.7
unnamed: P1.95, P33.6
unnamed: P1.107, P35.2
unnamed: P1.93, P33.4
unnamed: P1.92, P33.3
unnamed: P1.91, P33.2
unnamed: P1.90, P33.1
unnamed: P1.89, P32.8
unnamed: P1.88, P32.7
unnamed: P1.87, P32.6
unnamed: P1.86, P32.5
unnamed: P1.85, P32.4
unnamed: P1.84, P32.3
unnamed: P1.83, P32.2
unnamed: P1.82, P32.1
unnamed: P1.117, P24.1, P25.1
unnamed: P1.8, P2.3
unnamed: P1.7, P2.2
unnamed: P1.6, P2.1
unnamed: P1.120, P18.1, P19.1
unnamed: P1.118, P22.1, P23.1
unnamed: P1.61, P4.18
unnamed: P1.116, P26.1, P27.1
unnamed: P1.115, P28.1, P29.1
unnamed: P1.114, P30.1, P31.1
unnamed: P1.113, P35.8
unnamed: P1.112, P35.7
unnamed: P1.111, P35.6
unnamed: P1.110, P35.5
unnamed: P1.109, P35.4
unnamed: P1.108, P35.3
unnamed: P1.121, P16.1, P17.1
unnamed: P1.119, P20.1, P21.1
unnamed: P1.74, P5.12
unnamed: P1.81, P5.19
unnamed: P1.80, P5.18
unnamed: P1.79, P5.17
unnamed: P1.78, P5.16
unnamed: P1.77, P5.15
unnamed: P1.76, P5.14
unnamed: P1.75, P5.13
unnamed: P1.73, P5.11
unnamed: P1.72, P5.10
unnamed: P1.71, P5.9
unnamed: P1.70, P5.8
unnamed: P1.69, P5.7
unnamed: P1.68, P5.6
unnamed: P1.67, P5.5
unnamed: P1.66, P5.4
unnamed: P1.65, P5.3
unnamed: P1.64, P5.2
unnamed: P1.63, P5.1
unnamed: P1.62, P4.19
unnamed: P1.5, P6.1, P7.1
unnamed: P1.4, P8.1, P9.1
unnamed: P1.3, P10.1, P11.1
unnamed: P1.2, P12.1, P13.1
unnamed: P1.1, P14.1, P15.1
